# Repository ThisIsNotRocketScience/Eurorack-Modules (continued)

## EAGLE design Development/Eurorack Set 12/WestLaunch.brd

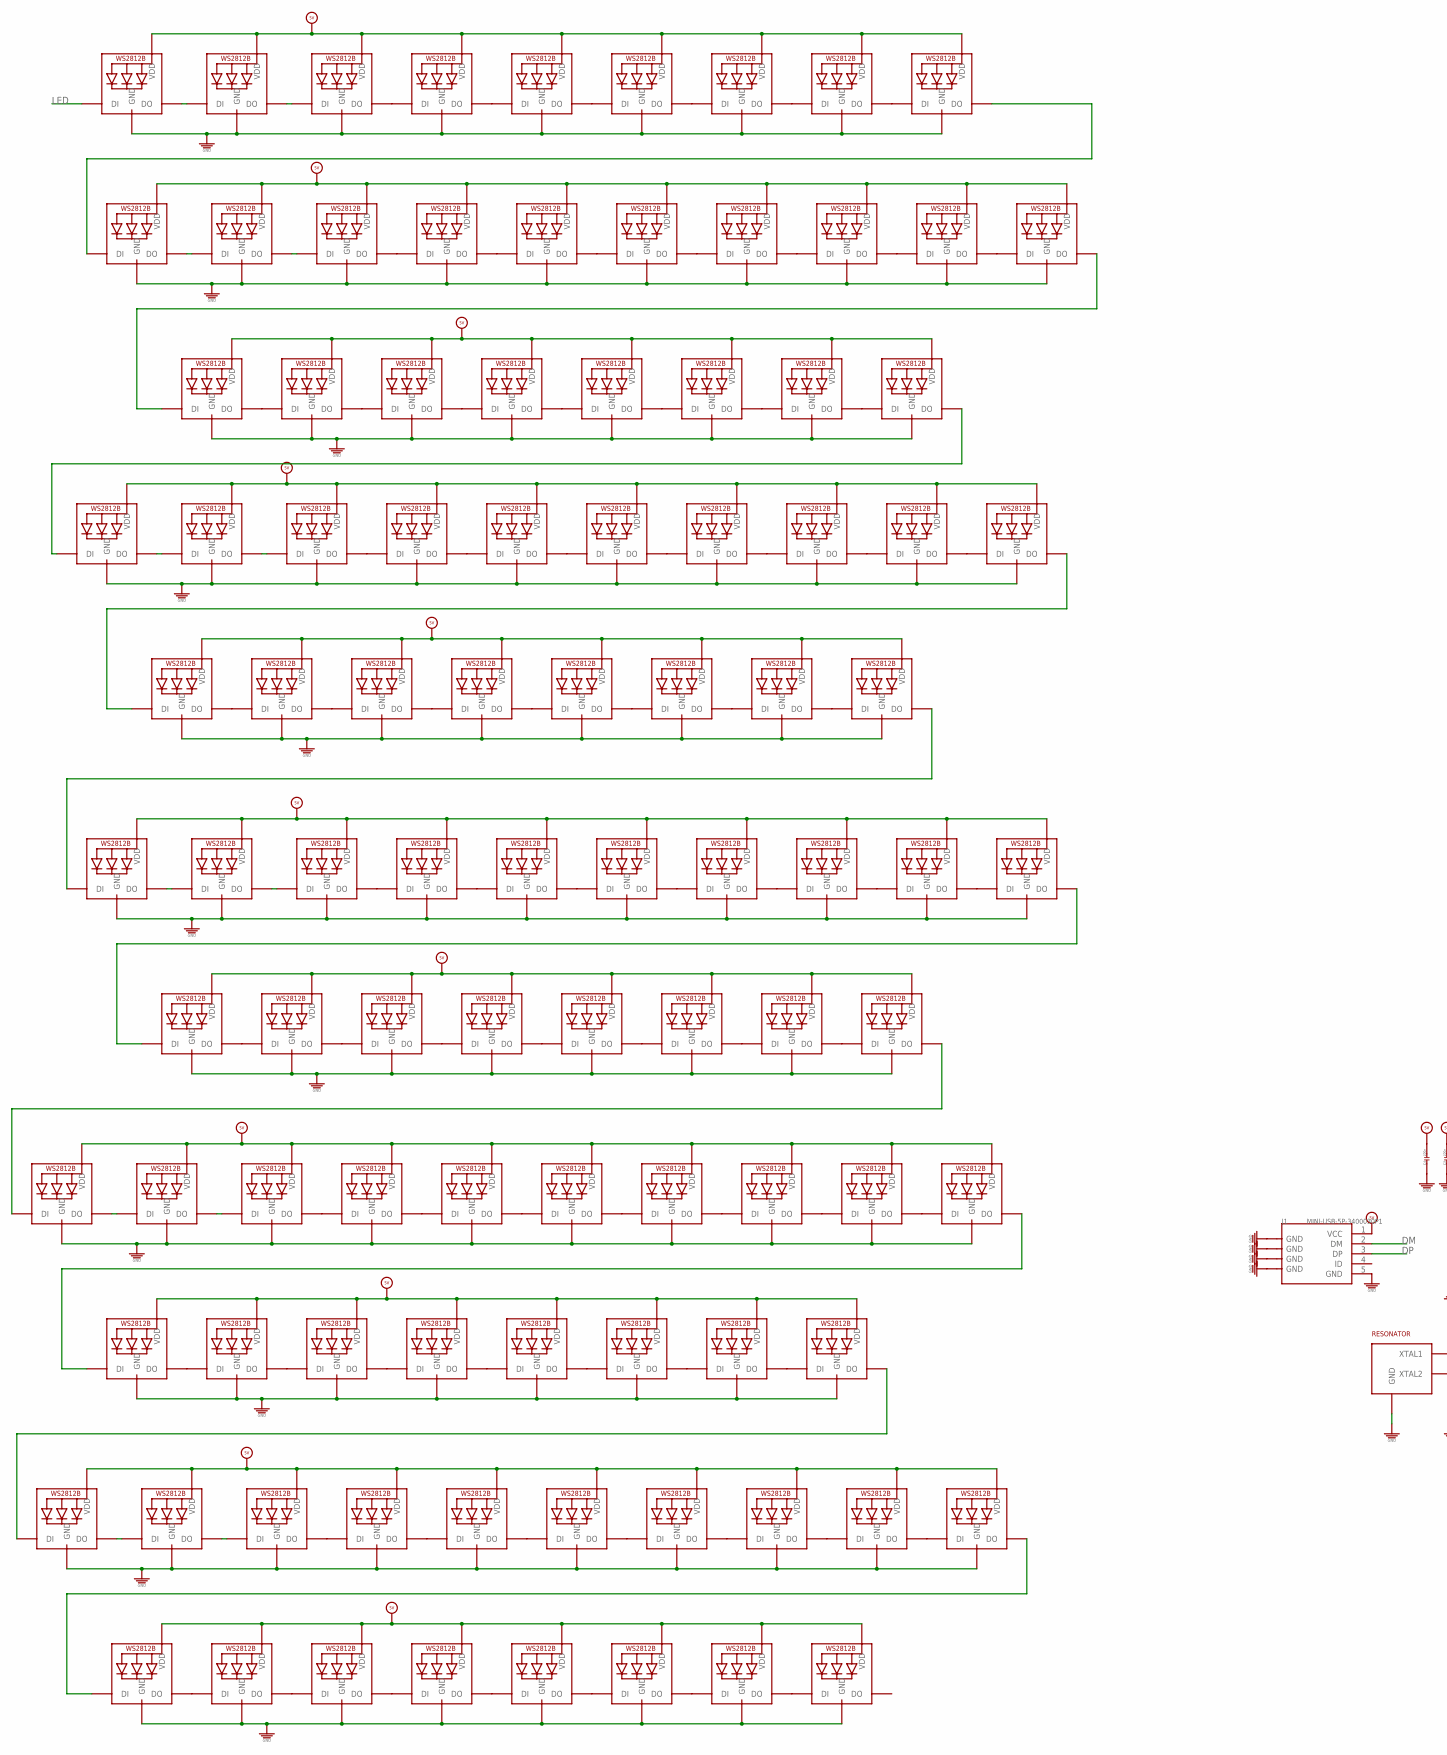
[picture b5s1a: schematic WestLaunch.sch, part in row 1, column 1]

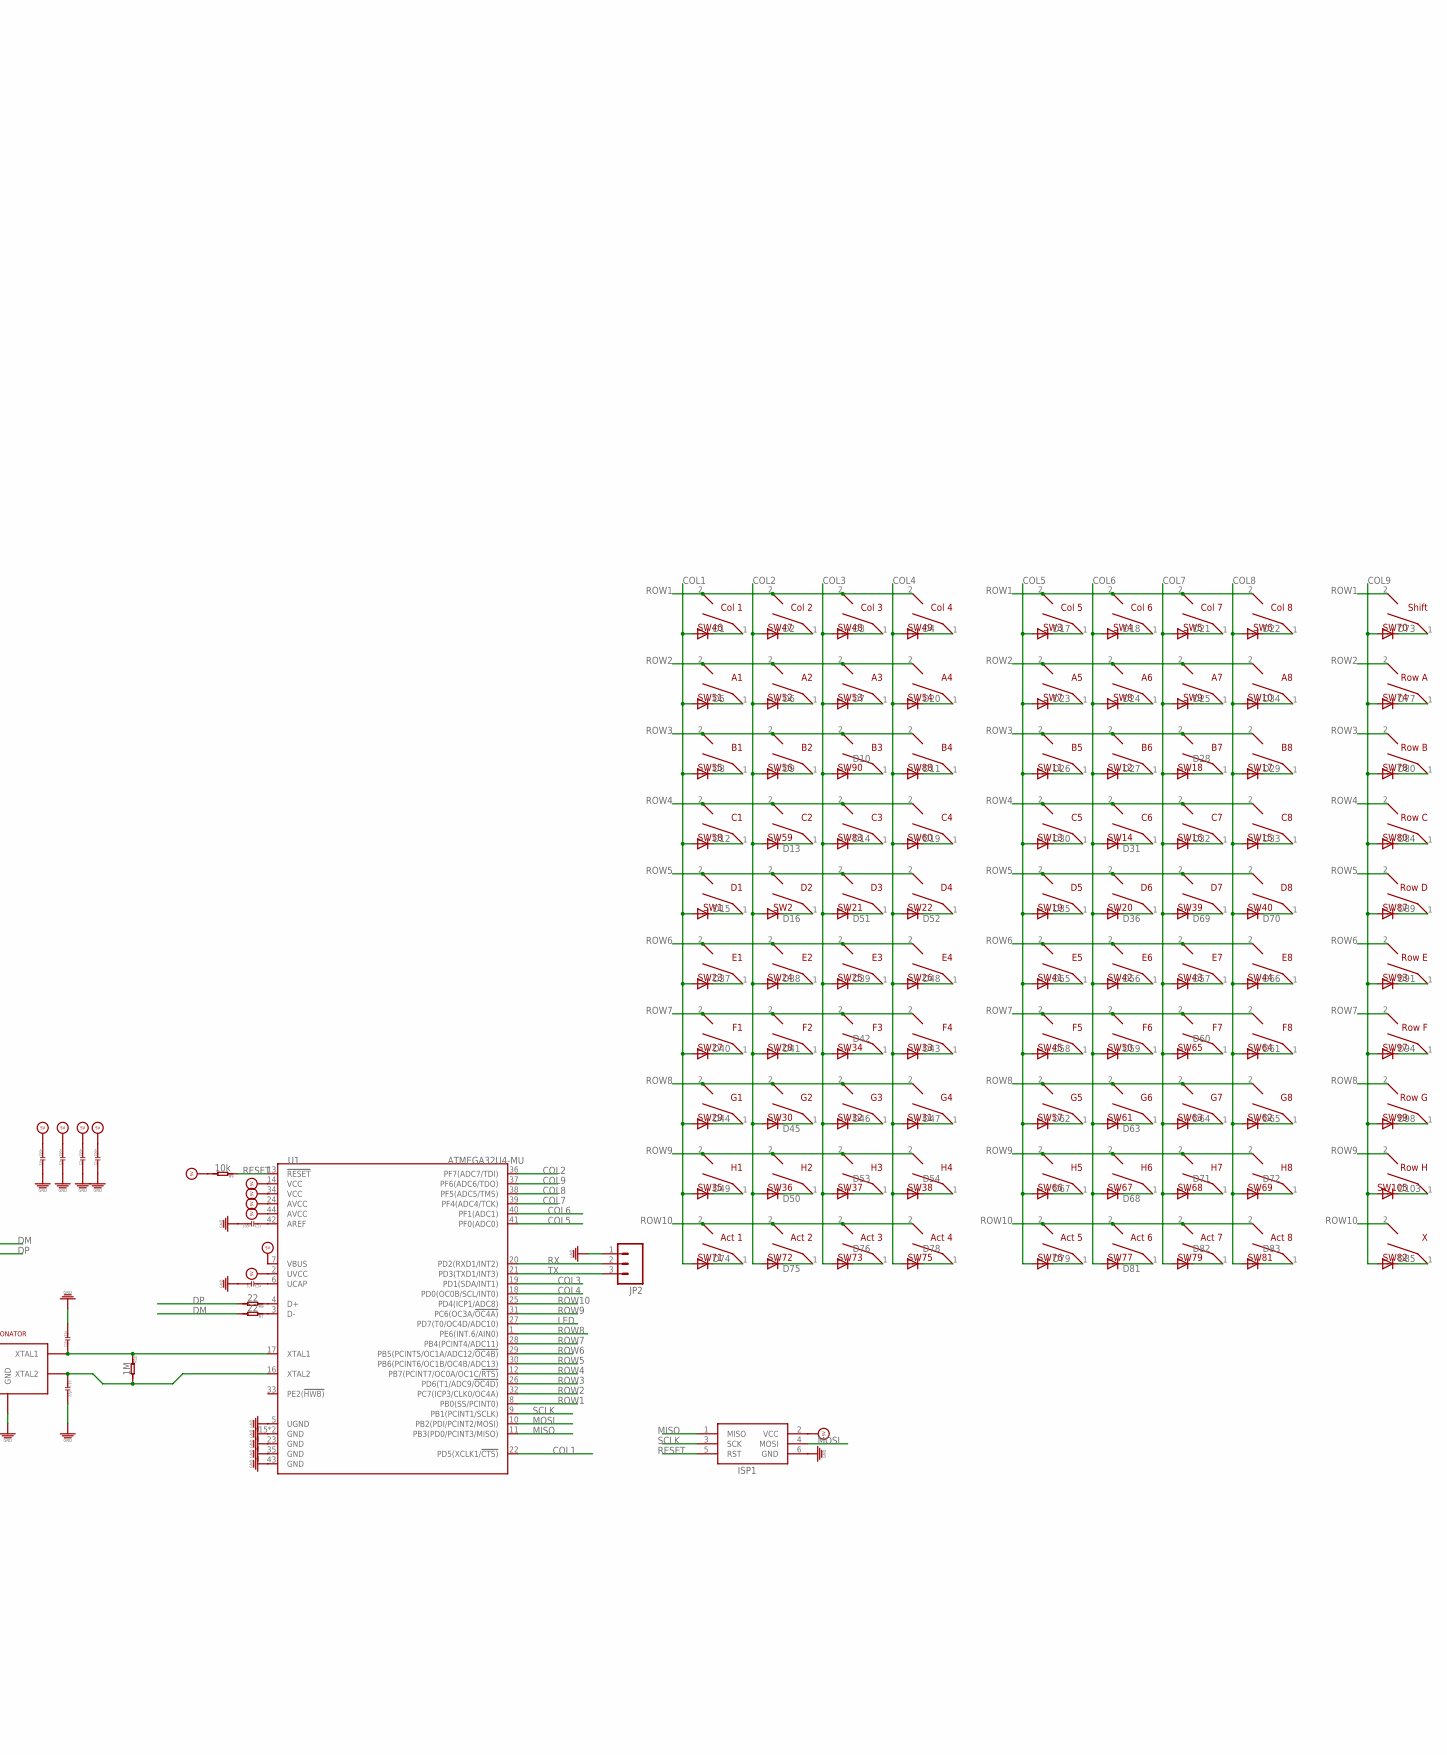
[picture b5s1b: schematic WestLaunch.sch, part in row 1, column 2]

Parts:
C1, C2, C3, C4, C13: 100n; C0603
C14: 1u; C0603
C15, C16: 22p; C0603
D1, D2, D3, D4, D5, D6, D7, D8, D9, D10, D11, D12, D13, D14, D15, D16, D17, D18, D19, D20, D21, D22, D23, D24, D25, D26, D27, D28, D29, D30, D31, D32, D33, D34, D35, D36, D37, D38, D39, D40, D41, D42, D43, D44, D45, D46, D47, D48, D49, D50, D51, D52, D53, D54, D55, D56, D57, D58, D59, D60, D61, D62, D63, D64, D65, D66, D67, D68, D69, D70, D71, D72, D73, D74, D75, D76, D77, D78, D79, D80, D81, D82, D83, D84, D85, D89, D91, D94, D98, D103: CGRM4001-G; SOD-123_MINI-SMA
ISP1: AVRISP-6; AVRISP
J1: MINI-USB-5P-3400030P1; MINI-B-5P-SMD
JP2: M03PTH; 1X03
LED1, LED2, LED3, LED4, LED5, LED6, LED7, LED8, LED9, LED10, LED11, LED12, LED13, LED14, LED15, LED16, LED17, LED18, LED19, LED20, LED21, LED22, LED23, LED24, LED25, LED26, LED27, LED28, LED29, LED30, LED31, LED32, LED33, LED34, LED35, LED36, LED37, LED38, LED39, LED40, LED41, LED42, LED43, LED44, LED45, LED46, LED47, LED48, LED49, LED50, LED51, LED52, LED53, LED54, LED55, LED56, LED57, LED58, LED59, LED60, LED61, LED62, LED63, LED64, LED65, LED66, LED67, LED68, LED69, LED70, LED71, LED72, LED73, LED74, LED75, LED76, LED77, LED78, LED79, LED80, LED81, LED82, LED83, LED84, LED85, LED86, LED87, LED88, LED89, LED90, LED91, LED92, LED93, LED94, LED95, LED96, LED97, LED98, LED99: WS2812B3535; LED3535
R7, R8: 22; R0603
R9: 10k; R0603
R10: 1M; R0603
SW1: D1; MX1A-XXNW
SW2: D2; MX1A-XXNW
SW3: Col 5; MX1A-XXNW
SW4: Col 6; MX1A-XXNW
SW5: Col 7; MX1A-XXNW
SW6: Col 8; MX1A-XXNW
SW7: A5; MX1A-XXNW
SW8: A6; MX1A-XXNW
SW9: A7; MX1A-XXNW
SW10: A8; MX1A-XXNW
SW11: B5; MX1A-XXNW
SW12: B6; MX1A-XXNW
SW13: C5; MX1A-XXNW
SW14: C6; MX1A-XXNW
SW15: C8; MX1A-XXNW
SW16: C7; MX1A-XXNW
SW17: B8; MX1A-XXNW
SW18: B7; MX1A-XXNW
SW19: D5; MX1A-XXNW
SW20: D6; MX1A-XXNW
SW21: D3; MX1A-XXNW
SW22: D4; MX1A-XXNW
SW23: E1; MX1A-XXNW
SW24: E2; MX1A-XXNW
SW25: E3; MX1A-XXNW
SW26: E4; MX1A-XXNW
SW27: F1; MX1A-XXNW
SW28: F2; MX1A-XXNW
SW29: G1; MX1A-XXNW
SW30: G2; MX1A-XXNW
SW31: G4; MX1A-XXNW
SW32: G3; MX1A-XXNW
SW33: F4; MX1A-XXNW
SW34: F3; MX1A-XXNW
SW35: H1; MX1A-XXNW
SW36: H2; MX1A-XXNW
SW37: H3; MX1A-XXNW
SW38: H4; MX1A-XXNW
SW39: D7; MX1A-XXNW
SW40: D8; MX1A-XXNW
SW41: E5; MX1A-XXNW
SW42: E6; MX1A-XXNW
SW43: E7; MX1A-XXNW
SW44: E8; MX1A-XXNW
SW45: F5; MX1A-XXNW
SW46: Col 1; MX1A-XXNW
SW47: Col 2; MX1A-XXNW
SW48: Col 3; MX1A-XXNW
SW49: Col 4; MX1A-XXNW
SW50: F6; MX1A-XXNW
SW51: A1; MX1A-XXNW
SW52: A2; MX1A-XXNW
SW53: A3; MX1A-XXNW
SW54: A4; MX1A-XXNW
SW55: B1; MX1A-XXNW
SW56: B2; MX1A-XXNW
SW57: G5; MX1A-XXNW
SW58: C1; MX1A-XXNW
SW59: C2; MX1A-XXNW
SW60: C4; MX1A-XXNW
SW61: G6; MX1A-XXNW
SW62: G8; MX1A-XXNW
SW63: G7; MX1A-XXNW
SW64: F8; MX1A-XXNW
SW65: F7; MX1A-XXNW
SW66: H5; MX1A-XXNW
SW67: H6; MX1A-XXNW
SW68: H7; MX1A-XXNW
SW69: H8; MX1A-XXNW
SW70: Shift; MX1A-XXNW
SW71: Act 1; MX1A-XXNW
SW72: Act 2; MX1A-XXNW
SW73: Act 3; MX1A-XXNW
SW74: Row A; MX1A-XXNW
SW75: Act 4; MX1A-XXNW
SW76: Act 5; MX1A-XXNW
SW77: Act 6; MX1A-XXNW
SW78: Row B; MX1A-XXNW
SW79: Act 7; MX1A-XXNW
SW80: Row C; MX1A-XXNW
SW81: Act 8; MX1A-XXNW
SW82: X; MX1A-XXNW
SW83: C3; MX1A-XXNW
SW87: Row D; MX1A-XXNW
SW88: B4; MX1A-XXNW
SW90: B3; MX1A-XXNW
SW93: Row E; MX1A-XXNW
SW97: Row F; MX1A-XXNW
SW99: Row G; MX1A-XXNW
SW105: Row H; MX1A-XXNW
U1: ATMEGA32U4-MU; QFN44
U$60: RESONATOR; 16MHZXTAL

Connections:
5V: C1.2, C2.2, C3.2, C4.2, ISP1.2 (VCC), J1.1 (VCC), LED1.1 (VDD), LED2.1 (VDD), LED3.1 (VDD), LED4.1 (VDD), LED5.1 (VDD), LED6.1 (VDD), LED7.1 (VDD), LED8.1 (VDD), LED9.1 (VDD), LED10.1 (VDD), LED11.1 (VDD), LED12.1 (VDD), LED13.1 (VDD), LED14.1 (VDD), LED15.1 (VDD), LED16.1 (VDD), LED17.1 (VDD), LED18.1 (VDD), LED19.1 (VDD), LED20.1 (VDD), LED21.1 (VDD), LED22.1 (VDD), LED23.1 (VDD), LED24.1 (VDD), LED25.1 (VDD), LED26.1 (VDD), LED27.1 (VDD), LED28.1 (VDD), LED29.1 (VDD), LED30.1 (VDD), LED31.1 (VDD), LED32.1 (VDD), LED33.1 (VDD), LED34.1 (VDD), LED35.1 (VDD), LED36.1 (VDD), LED37.1 (VDD), LED38.1 (VDD), LED39.1 (VDD), LED40.1 (VDD), LED41.1 (VDD), LED42.1 (VDD), LED43.1 (VDD), LED44.1 (VDD), LED45.1 (VDD), LED46.1 (VDD), LED47.1 (VDD), LED48.1 (VDD), LED49.1 (VDD), LED50.1 (VDD), LED51.1 (VDD), LED52.1 (VDD), LED53.1 (VDD), LED54.1 (VDD), LED55.1 (VDD), LED56.1 (VDD), LED57.1 (VDD), LED58.1 (VDD), LED59.1 (VDD), LED60.1 (VDD), LED61.1 (VDD), LED62.1 (VDD), LED63.1 (VDD), LED64.1 (VDD), LED65.1 (VDD), LED66.1 (VDD), LED67.1 (VDD), LED68.1 (VDD), LED69.1 (VDD), LED70.1 (VDD), LED71.1 (VDD), LED72.1 (VDD), LED73.1 (VDD), LED74.1 (VDD), LED75.1 (VDD), LED76.1 (VDD), LED77.1 (VDD), LED78.1 (VDD), LED79.1 (VDD), LED80.1 (VDD), LED81.1 (VDD), LED82.1 (VDD), LED83.1 (VDD), LED84.1 (VDD), LED85.1 (VDD), LED86.1 (VDD), LED87.1 (VDD), LED88.1 (VDD), LED89.1 (VDD), LED90.1 (VDD), LED91.1 (VDD), LED92.1 (VDD), LED93.1 (VDD), LED94.1 (VDD), LED95.1 (VDD), LED96.1 (VDD), LED97.1 (VDD), LED98.1 (VDD), LED99.1 (VDD), R9.2, U1.2 (UVCC), U1.7 (VBUS), U1.14 (VCC), U1.24 (AVCC), U1.34 (VCC), U1.44 (AVCC)
COL1: D1.A, D5.A, D8.A, D12.A, D15.A, D37.A, D40.A, D44.A, D49.A, D74.A, U1.22 (PD5(XCLK1/!CTS))
COL2: D2.A, D6.A, D9.A, D13.A, D16.A, D38.A, D41.A, D45.A, D50.A, D75.A, U1.36 (PF7(ADC7/TDI))
COL3: D3.A, D7.A, D10.A, D14.A, D39.A, D42.A, D46.A, D51.A, D53.A, D76.A, U1.19 (PD1(SDA/INT1))
COL4: D4.A, D11.A, D19.A, D20.A, D43.A, D47.A, D48.A, D52.A, D54.A, D78.A, U1.18 (PD0(OC0B/SCL/INT0))
COL5: D17.A, D23.A, D26.A, D30.A, D35.A, D55.A, D58.A, D62.A, D67.A, D79.A, U1.41 (PF0(ADC0))
COL6: D18.A, D24.A, D27.A, D31.A, D36.A, D56.A, D59.A, D63.A, D68.A, D81.A, U1.40 (PF1(ADC1))
COL7: D21.A, D25.A, D28.A, D32.A, D57.A, D60.A, D64.A, D69.A, D71.A, D82.A, U1.39 (PF4(ADC4/TCK))
COL8: D22.A, D29.A, D33.A, D34.A, D61.A, D65.A, D66.A, D70.A, D72.A, D83.A, U1.38 (PF5(ADC5/TMS))
COL9: D73.A, D77.A, D80.A, D84.A, D85.A, D89.A, D91.A, D94.A, D98.A, D103.A, U1.37 (PF6(ADC6/TDO))
DM: J1.2 (DM), R7.2
DP: J1.3 (DP), R8.2
GND: C1.1, C2.1, C3.1, C4.1, C13.2, C14.2, C15.2, C16.2, ISP1.6 (GND), J1.5 (GND), J1.GND@1 (GND), J1.GND@2 (GND), J1.GND@3 (GND), J1.GND@4 (GND), JP2.1, LED1.3 (GND), LED2.3 (GND), LED3.3 (GND), LED4.3 (GND), LED5.3 (GND), LED6.3 (GND), LED7.3 (GND), LED8.3 (GND), LED9.3 (GND), LED10.3 (GND), LED11.3 (GND), LED12.3 (GND), LED13.3 (GND), LED14.3 (GND), LED15.3 (GND), LED16.3 (GND), LED17.3 (GND), LED18.3 (GND), LED19.3 (GND), LED20.3 (GND), LED21.3 (GND), LED22.3 (GND), LED23.3 (GND), LED24.3 (GND), LED25.3 (GND), LED26.3 (GND), LED27.3 (GND), LED28.3 (GND), LED29.3 (GND), LED30.3 (GND), LED31.3 (GND), LED32.3 (GND), LED33.3 (GND), LED34.3 (GND), LED35.3 (GND), LED36.3 (GND), LED37.3 (GND), LED38.3 (GND), LED39.3 (GND), LED40.3 (GND), LED41.3 (GND), LED42.3 (GND), LED43.3 (GND), LED44.3 (GND), LED45.3 (GND), LED46.3 (GND), LED47.3 (GND), LED48.3 (GND), LED49.3 (GND), LED50.3 (GND), LED51.3 (GND), LED52.3 (GND), LED53.3 (GND), LED54.3 (GND), LED55.3 (GND), LED56.3 (GND), LED57.3 (GND), LED58.3 (GND), LED59.3 (GND), LED60.3 (GND), LED61.3 (GND), LED62.3 (GND), LED63.3 (GND), LED64.3 (GND), LED65.3 (GND), LED66.3 (GND), LED67.3 (GND), LED68.3 (GND), LED69.3 (GND), LED70.3 (GND), LED71.3 (GND), LED72.3 (GND), LED73.3 (GND), LED74.3 (GND), LED75.3 (GND), LED76.3 (GND), LED77.3 (GND), LED78.3 (GND), LED79.3 (GND), LED80.3 (GND), LED81.3 (GND), LED82.3 (GND), LED83.3 (GND), LED84.3 (GND), LED85.3 (GND), LED86.3 (GND), LED87.3 (GND), LED88.3 (GND), LED89.3 (GND), LED90.3 (GND), LED91.3 (GND), LED92.3 (GND), LED93.3 (GND), LED94.3 (GND), LED95.3 (GND), LED96.3 (GND), LED97.3 (GND), LED98.3 (GND), LED99.3 (GND), U1.5 (UGND), U1.15 (GND), U1.23 (GND), U1.35 (GND), U1.43 (GND), U1.TAB (GND), U$60.P$2 (GND), U$60.P$4 (GND)
LED: LED91.4 (DI), U1.27 (PD7(T0/OC4D/ADC10))
MISO: ISP1.1 (MISO), U1.11 (PB3(PD0/PCINT3/MISO))
MOSI: ISP1.4 (MOSI), U1.10 (PB2(PDI/PCINT2/MOSI))
unnamed: D1.C, SW46.1
unnamed: D2.C, SW47.1
unnamed: D3.C, SW48.1
unnamed: D4.C, SW49.1
unnamed: D5.C, SW51.1
unnamed: D6.C, SW52.1
unnamed: D7.C, SW53.1
unnamed: D8.C, SW55.1
unnamed: D9.C, SW56.1
unnamed: D10.C, SW90.1
unnamed: D11.C, SW88.1
unnamed: D12.C, SW58.1
unnamed: D13.C, SW59.1
unnamed: D14.C, SW83.1
unnamed: D15.C, SW1.1
unnamed: D16.C, SW2.1
unnamed: LED1.2 (DO), LED2.4 (DI)
unnamed: LED1.4 (DI), LED28.2 (DO)
unnamed: D19.C, SW60.1
unnamed: D20.C, SW54.1
unnamed: D17.C, SW3.1
unnamed: D18.C, SW4.1
unnamed: D21.C, SW5.1
unnamed: D22.C, SW6.1
unnamed: D23.C, SW7.1
unnamed: D24.C, SW8.1
unnamed: D25.C, SW9.1
unnamed: D26.C, SW11.1
unnamed: D27.C, SW12.1
unnamed: D28.C, SW18.1
unnamed: D29.C, SW17.1
unnamed: D30.C, SW13.1
unnamed: D31.C, SW14.1
unnamed: D32.C, SW16.1
unnamed: D33.C, SW15.1
unnamed: D34.C, SW10.1
unnamed: D35.C, SW19.1
unnamed: D36.C, SW20.1
unnamed: D37.C, SW23.1
unnamed: D38.C, SW24.1
unnamed: D39.C, SW25.1
unnamed: D40.C, SW27.1
unnamed: D41.C, SW28.1
unnamed: D42.C, SW34.1
unnamed: D43.C, SW33.1
unnamed: D44.C, SW29.1
unnamed: D45.C, SW30.1
unnamed: LED13.2 (DO), LED14.4 (DI)
unnamed: D46.C, SW32.1
unnamed: D47.C, SW31.1
unnamed: D48.C, SW26.1
unnamed: D49.C, SW35.1
unnamed: D50.C, SW36.1
unnamed: D51.C, SW21.1
unnamed: D52.C, SW22.1
unnamed: D53.C, SW37.1
unnamed: D54.C, SW38.1
unnamed: D55.C, SW41.1
unnamed: D56.C, SW42.1
unnamed: D57.C, SW43.1
unnamed: D58.C, SW45.1
unnamed: D59.C, SW50.1
unnamed: D60.C, SW65.1
unnamed: D61.C, SW64.1
unnamed: D62.C, SW57.1
unnamed: D63.C, SW61.1
unnamed: D64.C, SW63.1
unnamed: D65.C, SW62.1
unnamed: D66.C, SW44.1
unnamed: LED14.2 (DO), LED15.4 (DI)
unnamed: LED15.2 (DO), LED16.4 (DI)
unnamed: LED16.2 (DO), LED17.4 (DI)
unnamed: LED18.2 (DO), LED19.4 (DI)
unnamed: LED19.2 (DO), LED20.4 (DI)
unnamed: LED20.2 (DO), LED21.4 (DI)
unnamed: LED21.2 (DO), LED22.4 (DI)
unnamed: LED17.2 (DO), LED18.4 (DI)
unnamed: LED27.2 (DO), LED28.4 (DI)
unnamed: D67.C, SW66.1
unnamed: LED23.2 (DO), LED24.4 (DI)
unnamed: LED24.2 (DO), LED25.4 (DI)
unnamed: LED25.2 (DO), LED26.4 (DI)
unnamed: LED26.2 (DO), LED27.4 (DI)
unnamed: D68.C, SW67.1
unnamed: D69.C, SW39.1
unnamed: D70.C, SW40.1
unnamed: D71.C, SW68.1
unnamed: D72.C, SW69.1
unnamed: D73.C, SW70.1
unnamed: LED22.2 (DO), LED23.4 (DI)
unnamed: LED3.2 (DO), LED4.4 (DI)
unnamed: LED4.2 (DO), LED5.4 (DI)
unnamed: LED5.2 (DO), LED6.4 (DI)
unnamed: D77.C, SW74.1
unnamed: LED6.2 (DO), LED7.4 (DI)
unnamed: LED8.2 (DO), LED9.4 (DI)
unnamed: D80.C, SW78.1
unnamed: LED9.2 (DO), LED10.4 (DI)
unnamed: LED91.2 (DO), LED92.4 (DI)
unnamed: LED92.2 (DO), LED93.4 (DI)
unnamed: LED10.2 (DO), LED11.4 (DI)
unnamed: LED11.2 (DO), LED12.4 (DI)
unnamed: D84.C, SW80.1
unnamed: LED29.2 (DO), LED30.4 (DI)
unnamed: LED30.2 (DO), LED31.4 (DI)
unnamed: LED31.2 (DO), LED32.4 (DI)
unnamed: LED32.2 (DO), LED33.4 (DI)
unnamed: D89.C, SW87.1
unnamed: LED12.2 (DO), LED29.4 (DI)
unnamed: C13.1, U1.42 (AREF)
unnamed: R8.1, U1.4 (D+)
unnamed: D91.C, SW93.1
unnamed: LED7.2 (DO), LED8.4 (DI)
unnamed: LED33.2 (DO), LED34.4 (DI)
unnamed: D94.C, SW97.1
unnamed: LED35.2 (DO), LED36.4 (DI)
unnamed: R7.1, U1.3 (D-)
unnamed: C14.1, U1.6 (UCAP)
unnamed: C15.1, R10.1, U1.17 (XTAL1), U$60.P$1 (XTAL1)
unnamed: C16.1, R10.2, U1.16 (XTAL2), U$60.P$3 (XTAL2)
unnamed: LED34.2 (DO), LED35.4 (DI)
unnamed: LED37.2 (DO), LED38.4 (DI)
unnamed: D98.C, SW99.1
unnamed: LED38.2 (DO), LED39.4 (DI)
unnamed: LED39.2 (DO), LED40.4 (DI)
unnamed: LED40.2 (DO), LED41.4 (DI)
unnamed: LED42.2 (DO), LED43.4 (DI)
unnamed: D103.C, SW105.1
unnamed: LED43.2 (DO), LED44.4 (DI)
unnamed: LED44.2 (DO), LED45.4 (DI)
unnamed: LED45.2 (DO), LED46.4 (DI)
unnamed: LED47.2 (DO), LED48.4 (DI)
unnamed: LED48.2 (DO), LED49.4 (DI)
unnamed: LED49.2 (DO), LED50.4 (DI)
unnamed: LED50.2 (DO), LED51.4 (DI)
unnamed: LED46.2 (DO), LED47.4 (DI)
unnamed: LED41.2 (DO), LED42.4 (DI)
unnamed: LED51.2 (DO), LED52.4 (DI)
unnamed: LED53.2 (DO), LED54.4 (DI)
unnamed: LED52.2 (DO), LED53.4 (DI)
unnamed: LED55.2 (DO), LED56.4 (DI)
unnamed: LED56.2 (DO), LED57.4 (DI)
unnamed: LED57.2 (DO), LED58.4 (DI)
unnamed: LED58.2 (DO), LED59.4 (DI)
unnamed: LED60.2 (DO), LED61.4 (DI)
unnamed: LED61.2 (DO), LED62.4 (DI)
unnamed: LED62.2 (DO), LED63.4 (DI)
unnamed: LED63.2 (DO), LED64.4 (DI)
unnamed: LED65.2 (DO), LED66.4 (DI)
unnamed: LED66.2 (DO), LED67.4 (DI)
unnamed: LED67.2 (DO), LED68.4 (DI)
unnamed: LED68.2 (DO), LED69.4 (DI)
unnamed: LED64.2 (DO), LED65.4 (DI)
unnamed: LED59.2 (DO), LED60.4 (DI)
unnamed: LED69.2 (DO), LED70.4 (DI)
unnamed: LED71.2 (DO), LED72.4 (DI)
unnamed: LED70.2 (DO), LED71.4 (DI)
unnamed: LED73.2 (DO), LED74.4 (DI)
unnamed: LED74.2 (DO), LED75.4 (DI)
unnamed: LED75.2 (DO), LED76.4 (DI)
unnamed: LED76.2 (DO), LED77.4 (DI)
unnamed: LED78.2 (DO), LED79.4 (DI)
unnamed: LED79.2 (DO), LED80.4 (DI)
unnamed: LED80.2 (DO), LED81.4 (DI)
unnamed: LED81.2 (DO), LED82.4 (DI)
unnamed: LED83.2 (DO), LED84.4 (DI)
unnamed: LED84.2 (DO), LED85.4 (DI)
unnamed: LED85.2 (DO), LED86.4 (DI)
unnamed: LED86.2 (DO), LED87.4 (DI)
unnamed: LED82.2 (DO), LED83.4 (DI)
unnamed: LED77.2 (DO), LED78.4 (DI)
unnamed: LED87.2 (DO), LED88.4 (DI)
unnamed: LED89.2 (DO), LED90.4 (DI)
unnamed: LED88.2 (DO), LED89.4 (DI)
unnamed: LED2.2 (DO), LED3.4 (DI)
unnamed: LED36.2 (DO), LED37.4 (DI)
unnamed: LED54.2 (DO), LED55.4 (DI)
unnamed: LED72.2 (DO), LED73.4 (DI)
unnamed: D74.C, SW71.1
unnamed: D75.C, SW72.1
unnamed: D76.C, SW73.1
unnamed: D78.C, SW75.1
unnamed: D79.C, SW76.1
unnamed: D81.C, SW77.1
unnamed: D82.C, SW79.1
unnamed: D83.C, SW81.1
unnamed: D85.C, SW82.1
unnamed: LED93.2 (DO), LED94.4 (DI)
unnamed: LED94.2 (DO), LED95.4 (DI)
unnamed: LED96.2 (DO), LED97.4 (DI)
unnamed: LED97.2 (DO), LED98.4 (DI)
unnamed: LED98.2 (DO), LED99.4 (DI)
unnamed: LED13.4 (DI), LED99.2 (DO)
unnamed: LED95.2 (DO), LED96.4 (DI)
RESET: ISP1.5 (RST), R9.1, U1.13 (!RESET)
ROW1: SW3.2, SW4.2, SW5.2, SW6.2, SW46.2, SW47.2, SW48.2, SW49.2, SW70.2, U1.8 (PB0(SS/PCINT0))
ROW2: SW7.2, SW8.2, SW9.2, SW10.2, SW51.2, SW52.2, SW53.2, SW54.2, SW74.2, U1.32 (PC7(ICP3/CLK0/OC4A))
ROW3: SW11.2, SW12.2, SW17.2, SW18.2, SW55.2, SW56.2, SW78.2, SW88.2, SW90.2, U1.26 (PD6(T1/ADC9/!OC4D))
ROW4: SW13.2, SW14.2, SW15.2, SW16.2, SW58.2, SW59.2, SW60.2, SW80.2, SW83.2, U1.12 (PB7(PCINT7/OC0A/OC1C/!RTS))
ROW5: SW1.2, SW2.2, SW19.2, SW20.2, SW21.2, SW22.2, SW39.2, SW40.2, SW87.2, U1.30 (PB6(PCINT6/OC1B/OC4B/ADC13))
ROW6: SW23.2, SW24.2, SW25.2, SW26.2, SW41.2, SW42.2, SW43.2, SW44.2, SW93.2, U1.29 (PB5(PCINT5/OC1A/ADC12/!OC4B))
ROW7: SW27.2, SW28.2, SW33.2, SW34.2, SW45.2, SW50.2, SW64.2, SW65.2, SW97.2, U1.28 (PB4(PCINT4/ADC11))
ROW8: SW29.2, SW30.2, SW31.2, SW32.2, SW57.2, SW61.2, SW62.2, SW63.2, SW99.2, U1.1 (PE6(INT.6/AIN0))
ROW9: SW35.2, SW36.2, SW37.2, SW38.2, SW66.2, SW67.2, SW68.2, SW69.2, SW105.2, U1.31 (PC6(OC3A/!OC4A))
ROW10: SW71.2, SW72.2, SW73.2, SW75.2, SW76.2, SW77.2, SW79.2, SW81.2, SW82.2, U1.25 (PD4(ICP1/ADC8))
RX: JP2.2, U1.20 (PD2(RXD1/INT2))
SCLK: ISP1.3 (SCK), U1.9 (PB1(PCINT1/SCLK))
TX: JP2.3, U1.21 (PD3(TXD1/INT3))

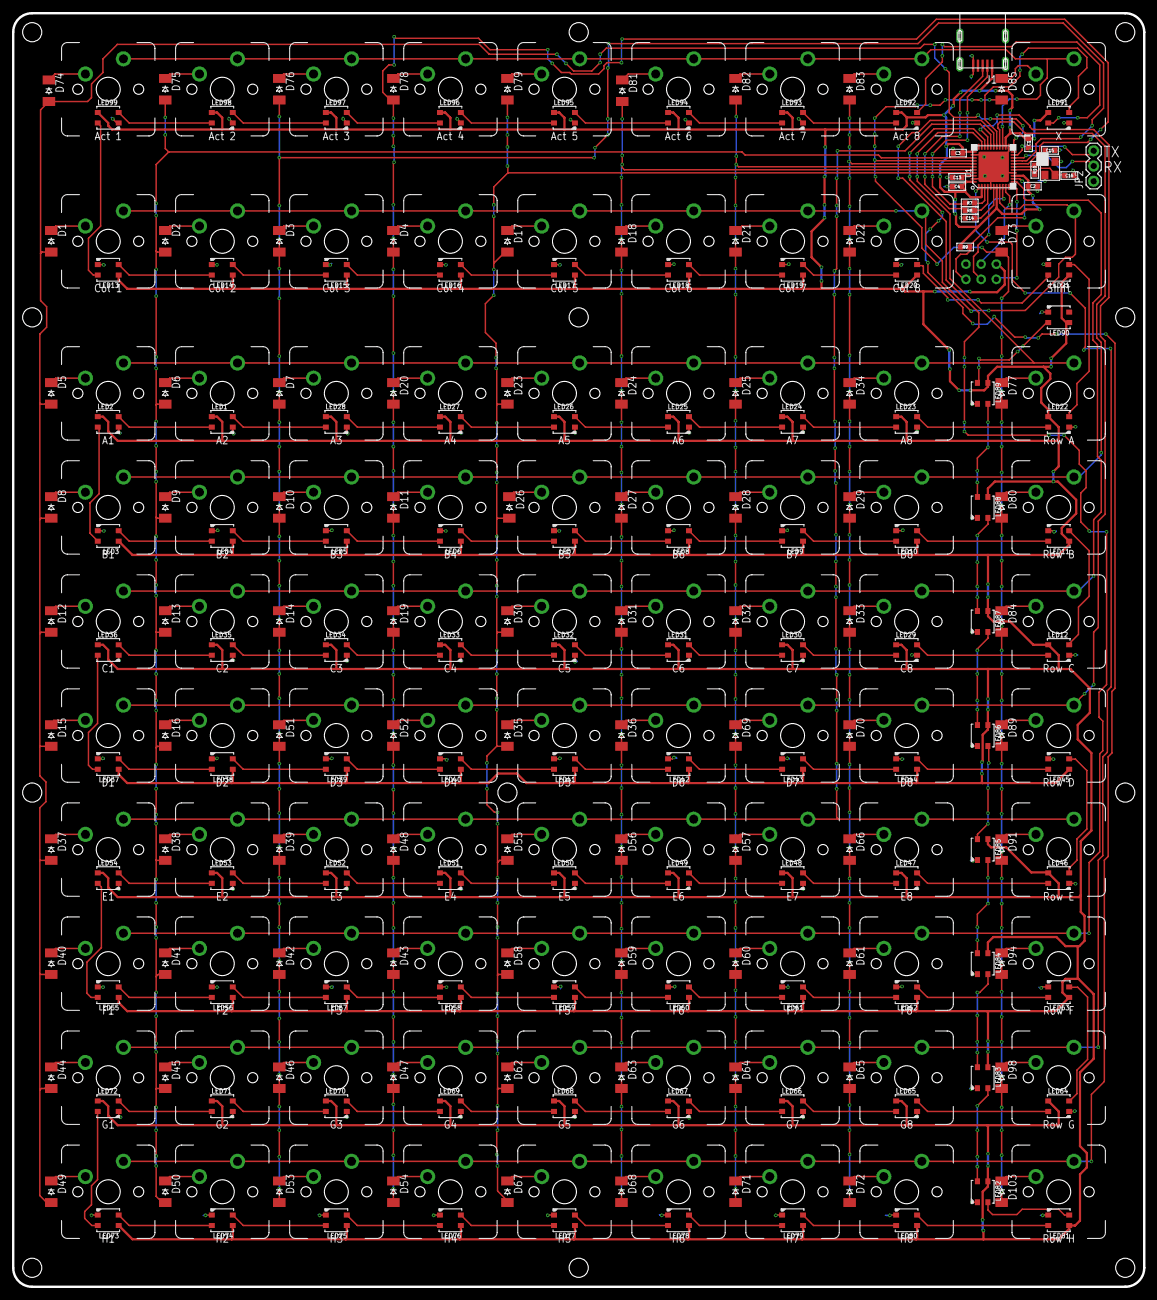
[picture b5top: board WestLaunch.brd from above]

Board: 2 copper layers, 188.9 x 212.7 mm, 296 parts (1 on the bottom side), 224 nets.

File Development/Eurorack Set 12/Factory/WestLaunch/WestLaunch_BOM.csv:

Comment,Designator,Footprint,LCSC Part #
CGRM4001-G,"D1, D10, D11, D12, D13, D14, D19, D2, D20, D3, D4, D5, D6, D7, D8, D9, D15, D16, D37, D38, D39, D40, D41, D42, D43, D44, D45, D46, D47, D48, D49, D50, D51, D52, D53, D54, D17, D18, D21, D22, D23, D24, D25, D26, D27, D28, D29, D30, D31, D32, D33, D34, D35, D36, D55, D56, D57, D58, D59, D60, D61, D62, D63, D64, D65, D66, D67, D68, D69, D70, D71, D72, D73, D77, D80, D84, D89, D91, D94, D98, D103, D74, D75, D76, D78, D79, D81, D82, D83, D85",SOD-123_MINI-SMA,
Col 1,"SW46",MX1A-XXNW,
Col 2,"SW47",MX1A-XXNW,
Col 3,"SW48",MX1A-XXNW,
Col 4,"SW49",MX1A-XXNW,
A1,"SW51",MX1A-XXNW,
A2,"SW52",MX1A-XXNW,
A3,"SW53",MX1A-XXNW,
A4,"SW54",MX1A-XXNW,
B1,"SW55",MX1A-XXNW,
B2,"SW56",MX1A-XXNW,
C1,"SW58",MX1A-XXNW,
C2,"SW59",MX1A-XXNW,
C4,"SW60",MX1A-XXNW,
C3,"SW83",MX1A-XXNW,
B4,"SW88",MX1A-XXNW,
B3,"SW90",MX1A-XXNW,
D1,"SW1",MX1A-XXNW,
D2,"SW2",MX1A-XXNW,
D3,"SW21",MX1A-XXNW,
D4,"SW22",MX1A-XXNW,
E1,"SW23",MX1A-XXNW,
E2,"SW24",MX1A-XXNW,
E3,"SW25",MX1A-XXNW,
E4,"SW26",MX1A-XXNW,
F1,"SW27",MX1A-XXNW,
F2,"SW28",MX1A-XXNW,
G1,"SW29",MX1A-XXNW,
G2,"SW30",MX1A-XXNW,
G4,"SW31",MX1A-XXNW,
G3,"SW32",MX1A-XXNW,
F4,"SW33",MX1A-XXNW,
F3,"SW34",MX1A-XXNW,
H1,"SW35",MX1A-XXNW,
H2,"SW36",MX1A-XXNW,
H3,"SW37",MX1A-XXNW,
H4,"SW38",MX1A-XXNW,
Col 5,"SW3",MX1A-XXNW,
Col 6,"SW4",MX1A-XXNW,
Col 7,"SW5",MX1A-XXNW,
Col 8,"SW6",MX1A-XXNW,
A5,"SW7",MX1A-XXNW,
A6,"SW8",MX1A-XXNW,
A7,"SW9",MX1A-XXNW,
A8,"SW10",MX1A-XXNW,
B5,"SW11",MX1A-XXNW,
B6,"SW12",MX1A-XXNW,
C5,"SW13",MX1A-XXNW,
C6,"SW14",MX1A-XXNW,
C8,"SW15",MX1A-XXNW,
C7,"SW16",MX1A-XXNW,
B8,"SW17",MX1A-XXNW,
B7,"SW18",MX1A-XXNW,
D5,"SW19",MX1A-XXNW,
D6,"SW20",MX1A-XXNW,
D7,"SW39",MX1A-XXNW,
D8,"SW40",MX1A-XXNW,
E5,"SW41",MX1A-XXNW,
E6,"SW42",MX1A-XXNW,
E7,"SW43",MX1A-XXNW,
E8,"SW44",MX1A-XXNW,
F5,"SW45",MX1A-XXNW,
F6,"SW50",MX1A-XXNW,
G5,"SW57",MX1A-XXNW,
G6,"SW61",MX1A-XXNW,
G8,"SW62",MX1A-XXNW,
G7,"SW63",MX1A-XXNW,
F8,"SW64",MX1A-XXNW,
F7,"SW65",MX1A-XXNW,
H5,"SW66",MX1A-XXNW,
H6,"SW67",MX1A-XXNW,
H7,"SW68",MX1A-XXNW,
H8,"SW69",MX1A-XXNW,
Shift,"SW70",MX1A-XXNW,
Row A,"SW74",MX1A-XXNW,
Row B,"SW78",MX1A-XXNW,
Row C,"SW80",MX1A-XXNW,
Row D,"SW87",MX1A-XXNW,
Row E,"SW93",MX1A-XXNW,
Row F,"SW97",MX1A-XXNW,
Row G,"SW99",MX1A-XXNW,
Row H,"SW105",MX1A-XXNW,
Act 1,"SW71",MX1A-XXNW,
Act 2,"SW72",MX1A-XXNW,
Act 3,"SW73",MX1A-XXNW,
Act 4,"SW75",MX1A-XXNW,
Act 5,"SW76",MX1A-XXNW,
Act 6,"SW77",MX1A-XXNW,
Act 7,"SW79",MX1A-XXNW,
Act 8,"SW81",MX1A-XXNW,
X,"SW82",MX1A-XXNW,
WS2812B3535,"LED13, LED14, LED15, LED16, LED17, LED18, LED19, LED20, LED21, LED22, LED23, LED24, LED25, LED26, LED27, LED28, LED1, LED2, LED3, LED4, LED5, LED6, LED7, LED8, LED9, LED10, LED11, LED12, LED29, LED30, LED31, LED32, LED33, LED34, LED35, LED36, LED37, LED38, LED39, LED40, LED41, LED42, LED43, LED44, LED45, LED46, LED47, LED48, LED49, LED50, LED51, LED52, LED53, LED54, LED55, LED56, LED57, LED58, LED59, LED60, LED61, LED62, LED63, LED64, LED65, LED66, LED67, LED68, LED69, LED70, LED71, LED72, LED73, LED74, LED75, LED76, LED77, LED78, LED79, LED80, LED81, LED82, LED83, LED84, LED85, LED86, LED87, LED88, LED89, LED90, LED91, LED92, LED93, LED94, LED95, LED96, LED97, LED98, LED99",LED3535,
ATMEGA32U4-MU,"U1",QFN44,
22,"R7, R8",R0603,
10k,"R9",R0603,
1M,"R10",R0603,
100n,"C13, C1, C2, C3, C4",C0603,
1u,"C14",C0603,
22p,"C15, C16",C0603,
AVRISP-6,"ISP1",AVRISP,
RESONATOR,"U$60",16MHZXTAL,
,"JP2",1X03,
MINI-USB-5P-3400030P1,"J1",MINI-B-5P-SMD,
